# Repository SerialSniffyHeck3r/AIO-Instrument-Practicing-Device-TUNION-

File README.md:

# STM32F4 Portable Practice DSP Device

## Videos

https://www.youtube.com/watch?v=_CYvJwdOhUQ  Recovering Data

https://www.youtube.com/watch?v=7vPy3JID6l4  System Settings

https://www.youtube.com/watch?v=G-kPSslMNc0  BPM Auto Calculation

https://www.youtube.com/watch?v=HqbBY2KLgDY  Hardware Self Test

https://www.youtube.com/watch?v=8V4moodQUs4  Music Play Mode

https://www.youtube.com/watch?v=r6egSswZjCg  Notch Filter Applied

https://www.youtube.com/watch?v=-oUxMyITEes  Pitch Shifter Applied

https://www.youtube.com/watch?v=r_tZYo8vfbs  Volume Sound Effect

## Overview

This was developed for my bachelor graduation project, but with keeping in mind that the device will be used personally.. or crowdfunded.
It turned out it wasn't that good to be crowdfunded.. but still it works! and also good for my personal use.

This project focuses on developing a **portable practice companion** built around an **STM32F407** microcontroller.  
The device helps people practice instruments at home or in a rehearsal room without that huge amount of bulky gears.

## TL;DR (for recruiters)

- **Platform:** STM32F407, dual I2S audio, RGB 16x2 LCD, LED bar, rotary encoder, Li-ion battery
- **Focus:** Real-time audio DSP for instrument practice (notch filter, pitch shift, mixer), tuner, metronome
- **Reliability:** Flash config storage with CRC and wear-leveling, backup SRAM snapshot, factory self-test mode
- **Result:** Fully working handheld prototype with custom PCB, firmware, and UX

## STM32F4 기반 악기 연습 장치 'Tunion': 한국어 설명

해당 레포지토리는 본인의 졸업 작품으로써 설게한 제품에 대해 다루고 있습니다.

가정 및 연습실 환경에서는 악기를 크게 연주할 수 없어 뮤트를 착용하거나 전자 악기를 연주하게 된다는 문제 의식에서 출발하였으며, 악기 케이스에 항상 휴대하고 다닐 수 있으면서 악기를 연주할 때 바로 꺼내서 사용할 수 있는 만능 장비를 목표로 개발되었습니다. 
- 반주를 듣고, 반주가 없을 때 아무 음원이나 틀어서 Notch Filter를 적용하여 본인이 연주하는 악기 대역만 잘라서 그 부분과 본인의 악기 소리를 같이 들으면서 연습하거나
- 비트 및 서브비트 등 다양한 기능이 포함된 메트로놈 소리를 들으면서 반주도 같이 듣고 그 소리에 맞춰 악기를 연습하거나
- 악기를 조율하거나
- 또는 악기를 적절한 온습도의 환경에서 보관할 수 있게 하는 것

을 목표로 두고 있습니다.

본 기기의 기능은 다음과 같습니다:
- 악기로부터 들어오는 악기 소리 아날로그 입력 / 음향기기로부터 들어오는 반주 입력을 믹싱 및 개별 볼륨 조절
- 반주에서 본인이 연주하고자 하는 악기 대역을 자를 수 있는 Notch Filter를 적용해서 악기 소리와 믹싱
- HSE를 통해 달성한 고정밀 메트로놈, Sub-Beat, Tap Tempo, 리타르단도 기능을 포함하는 시중에도 찾아보기 힘든 다기능 메트로놈
- 악기 튜너 및 펑션 제너레이터
- 환경설정 및 Flash와 백업 SRAM에 환경설정 다중 백업
- Real-Time Clock, 연습 시간 기록 기능
- 실제 생산을 위한 하드웨어 셀프 테스트 (RAM, Flash 접근 시간 테스트, LCD 및 오디오 출력 테스트)
- 스스로의 펌웨어를 알아서 '죽이는' 히든 커맨드

### 기기 내부 저장 방식

본인을 레트로 컴퓨팅에 관심이 많으며, 레트로 컴퓨팅을 연구하거나 임베디드 시스템을 개인적으로 연구하면서 생긴 아이디어를 적용했습니다.

MCU와 내부 RAM이 살아 있는 상황에서
- Flash에 저장하는 경우: 홈 화면으로 복귀 / 절전 모드에서 탈출했을 때 설정 값이 이전과 변화했을 경우에만 Write
- BKPSRAM에 저장하는 경우: 모든 버튼이 조작되었을 때. Overhead가 낮아 최대 1초에 30번을 조작해도 시스템의 동작 안정성을 저해하지 않는다는 판단.

전원이 완전히 차단되었으나 백업 전지는 살아 있는 경우:
- 전원 인가시 BKPSRAM의 값 확인 후, Magic Number (0xDEADBEEF) Check
- 백업 전지가 살아 있으므로 Magic Number가 그대로 있으므로 유효하다고 판단하여, BKPSRAM에서 바로 값을 불러옴

전원이 완전히 차단되고 백업 배터리까지 빠졌을 경우:
- 전원 인가시 BKPSRAM의 값 확인 후 Magic Number가 유효하지 않음을 확인
- 사용자에게 Recover Data? YES / NO 인터페이스를 통해, 백업 배터리 분리가 초기화를 위한 의도적 행동인지 확인.
- 만약 YES를 선택했을 경우, FLASH에서 값을 복원. NO를 선택했을 경우 시스템 설정이 출고 시와 동일하게 초기화됨.
- 어차피 백업 배터리가 분리되었으면 **당연히** RTC도 유효하지 않을 것이므로, Yes / No 선택 유무에 상관없이 시계 재설정 유도
- 이후 정상 부팅 

---

## Backstory

I play lots of instrument from woodwinds to percussion. Music is pretty much literally my life. 
When I practice guitar or other instruments at home, 
I usually need shitloads of separate devices: audio interface, mixer, tuner, metronome, maybe a laptop? a phone??

So this is the backstory. I just wanted a **single small device** that can do all of these, while maintaining the functionality.
This is a graduation project, but my intention was to make something that is actually useful and is potentially lucrative.

The function that I planned to implement was:
- mix backing track and my instrument,
- remove some frequency range (for example vocals),
- quickly transpose the song,
- show audio level
- tuner and metromone with lots of features
- features that every portable embedded device that is on sale should have

So I designed and built this device as my **bachelor graduation project**.

---

## What this device does

From a user point of view, this box is:

- A **small mixer** for two stereo audio sources
- A **practice helper** that can cut or change a specific frequency band, then mix audio with my instrument sound
- A **digital tuner** with 1 cent resolution
- A **metronome** with different time signatures and tempo changes
- A **status monitor** for battery, temperature, humidity and system state

All of this runs on one STM32F407 MCU with no external DSP chip.

---

## Main features

### 1. Real-time audio DSP pipeline

- Two I2S inputs (for example: backing track + instrument/mic)
- DMA double-buffered ring pipeline (16-bit audio → float → processed → 16-bit)
- **Real-time mixing** of both channels with:
  - 50-step digital volume for each channel
  - master volume and balance
  - dBFS level meters for input level check

### 2. Adjustable band-cut / notch filter for practice

- User can select a **frequency range to cut** (for example vocal range)
- Implemented with **ARM CMSIS-DSP IIR biquad filters**
- Supports:
  - on/off control from the UI
  - start / end frequency
  - **three user presets** per instrument (saved in non-volatile memory)

This lets me listen to a song while removing or reducing the part I want to practice over.

### 3. Simple pitch shift for fast transposition

- Integrated **pitch shift** engine for quick transpose
- Control in **semitones** (for example −3…+3)
- Focus is on **low latency** and “good enough for practice”,  
  not studio-quality offline processing

### 4. Integrated tuner

- **Digital chromatic tuner** with 1-cent resolution
- AMDF-based pitch detection with:
  - harmonic / octave correction
  - pre-lock and lock logic to avoid jumping notes
- Adjustable:
  - **A4 base frequency** (calibration)
  - input sensitivity

The tuner drives both the LCD and the LED bar for visual feedback.

### 5. Sample-accurate metronome & tone generator

- Metronome audio is generated **inside the same DSP pipeline** as the audio
- Features:
  - accents and sub-clicks
  - tempo changes (ritardando / accelerando / back to a-tempo)
  - separate metronome volume
- Extra **sound generator mode** (sine / square / triangle)  
  for tuning or quick tests.

### 6. User interface and UX

- **RGB 16x2 character LCD** (HD44780-compatible)
  - custom UI pages for each mode (practice, tuner, metronome, settings)
- **LED bar** driven by PWM:
  - VU meter for input / mic levels
  - tuner center indication
  - metronome visualization
- **Rotary encoder + buttons**:
  - used for navigation and parameter editing
  - single short/long click design so it can be used while holding an instrument

I tried to keep the UI simple enough to use with one hand.

### 7. Power, environment and settings

- Powered from a **single Li-ion battery**
- Battery:
  - voltage measurement and level estimation
  - low-battery handling
- **Temperature & humidity** sensor (DHT22):
  - shows instrument storage environment
- **Config storage:**
  - main storage in Flash (sector with custom format)
  - record format with version, sequence number and CRC32
  - background service that only writes when values changed
- **Backup snapshot:**
  - second copy in backup SRAM,  
    so the device can restore settings quickly after a battery change

### 8. Factory / test mode

- Hidden button combo opens a **self-test mode**
- Used for:
  - LCD and LED test
  - audio path test
  - peripheral checks
- This was designed with **future production / repair** in mind.

---

## Hardware overview

- MCU: **STM32F407** (Cortex-M4 with FPU and DSP extensions)
- Audio:
  - Dual I2S interface
  - 16-bit stereo in/out
- UI:
  - HD44780-compatible RGB 16x2 LCD
  - 10-segment (or similar) LED bar
  - rotary encoder + buttons
- Sensors:
  - DHT22 temperature / humidity
  - battery voltage measurement
- Power:
  - Li-ion battery
  - backup power for RTC and SRAM

Custom PCB was designed so that the device is actually **hand-held and portable**. 

---

## Firmware / code structure (short version)

The firmware is written in **C** using the STM32 HAL and CMSIS-DSP.

- `main.c`  
  - main UI state machine, mode handling, LCD updates
- `notch.c`  
  - audio DSP pipeline, I2S callback, mixing, notch filter, pitch shift, metronome, sound generator
- `tuner.c`  
  - pitch detection and note / cent calculation
- `LEDcontrol.c`  
  - LED bar effects, VU meter and tuner / metronome visualization
- `BatteryTemp.c`, `dht.c`  
  - battery and DHT22 handling
- `PowerFlash.c`  
  - Flash config storage with CRC and wear-leveling
- `PowerSave.c`  
  - backup SRAM snapshot for fast resume
- `Clock.c`  
  - RTC time setting UI

The code is clearly not perfect, as this is one of my first huge system architect project.
but it is a complete prototype that I could really use as my **daily practice companion**.

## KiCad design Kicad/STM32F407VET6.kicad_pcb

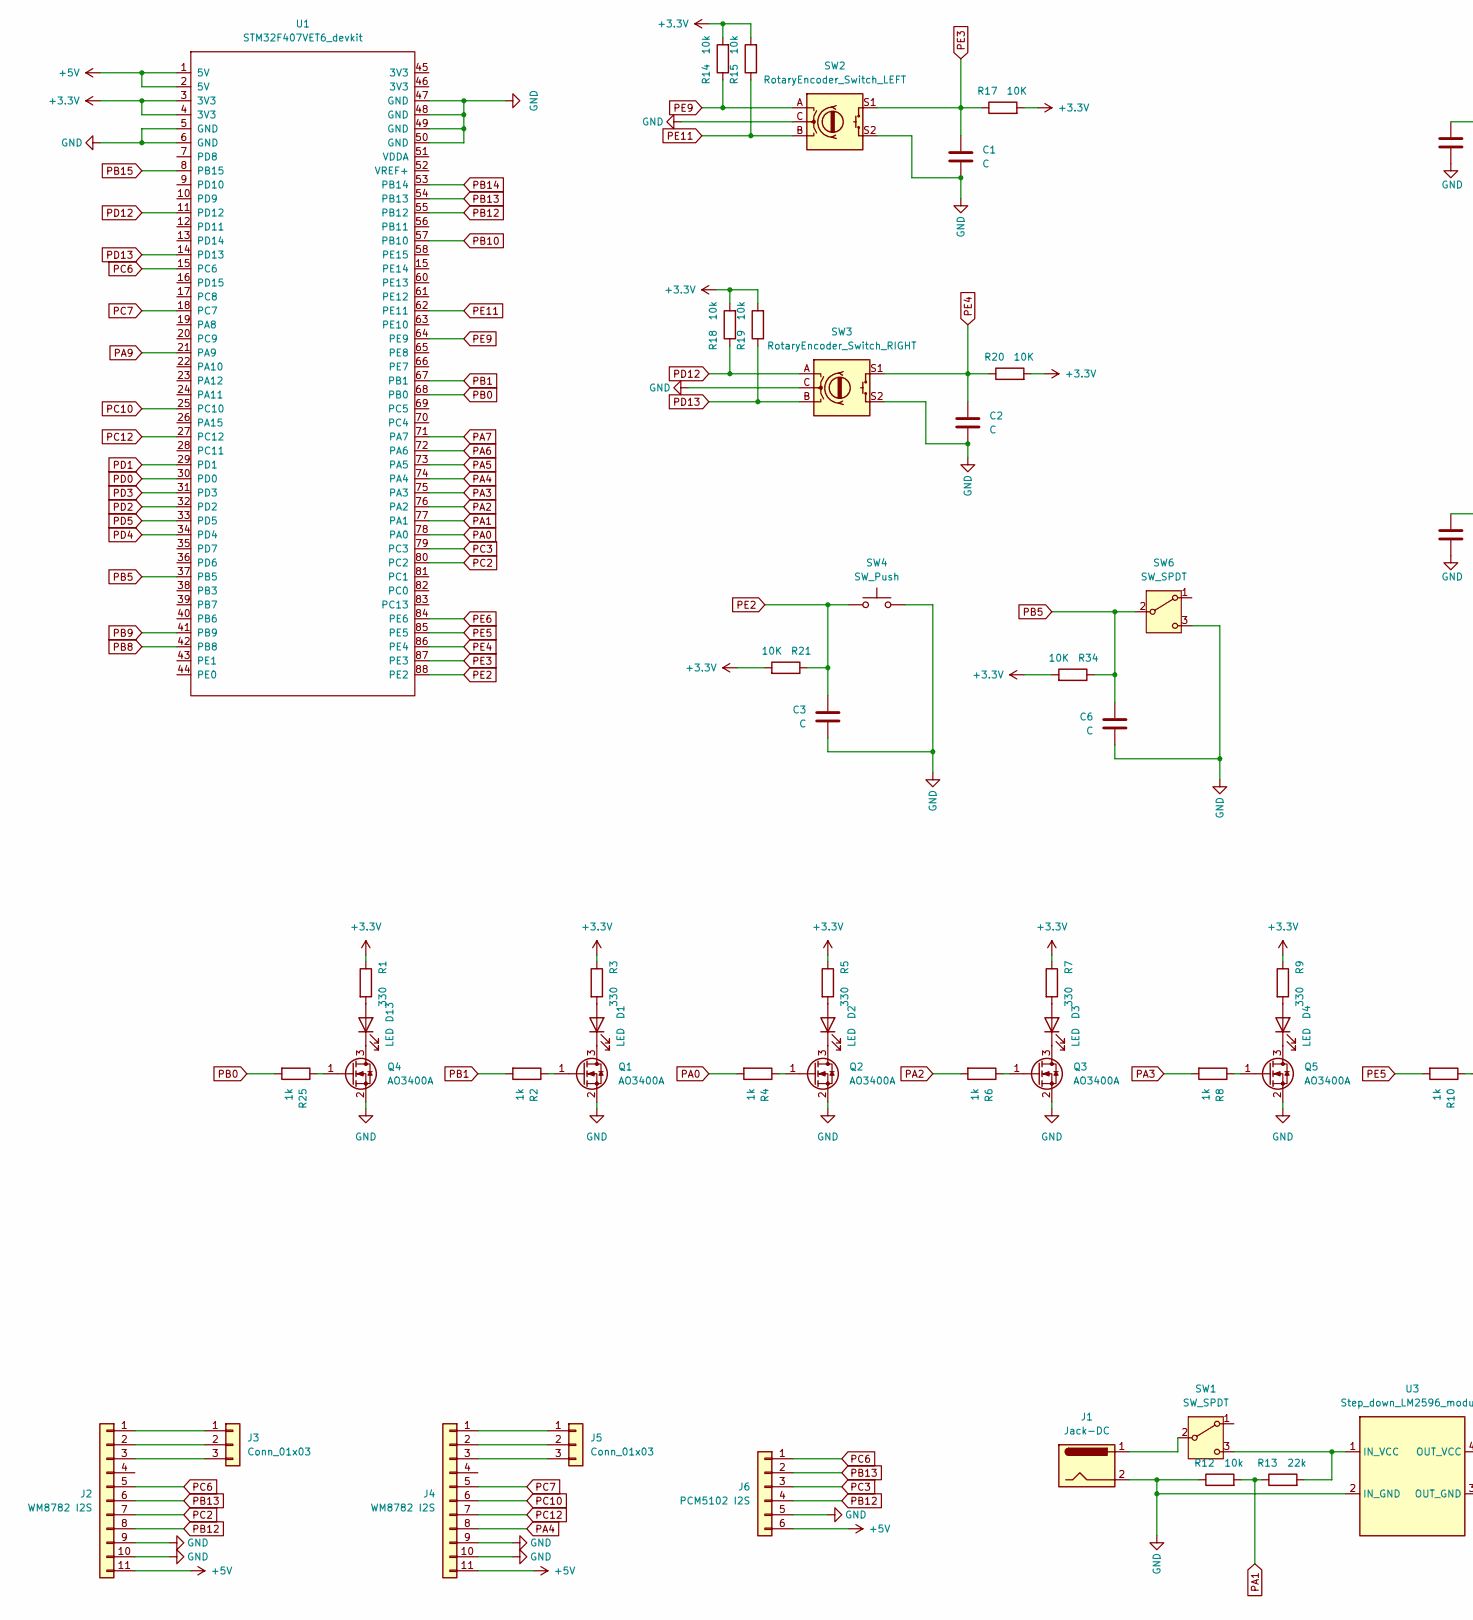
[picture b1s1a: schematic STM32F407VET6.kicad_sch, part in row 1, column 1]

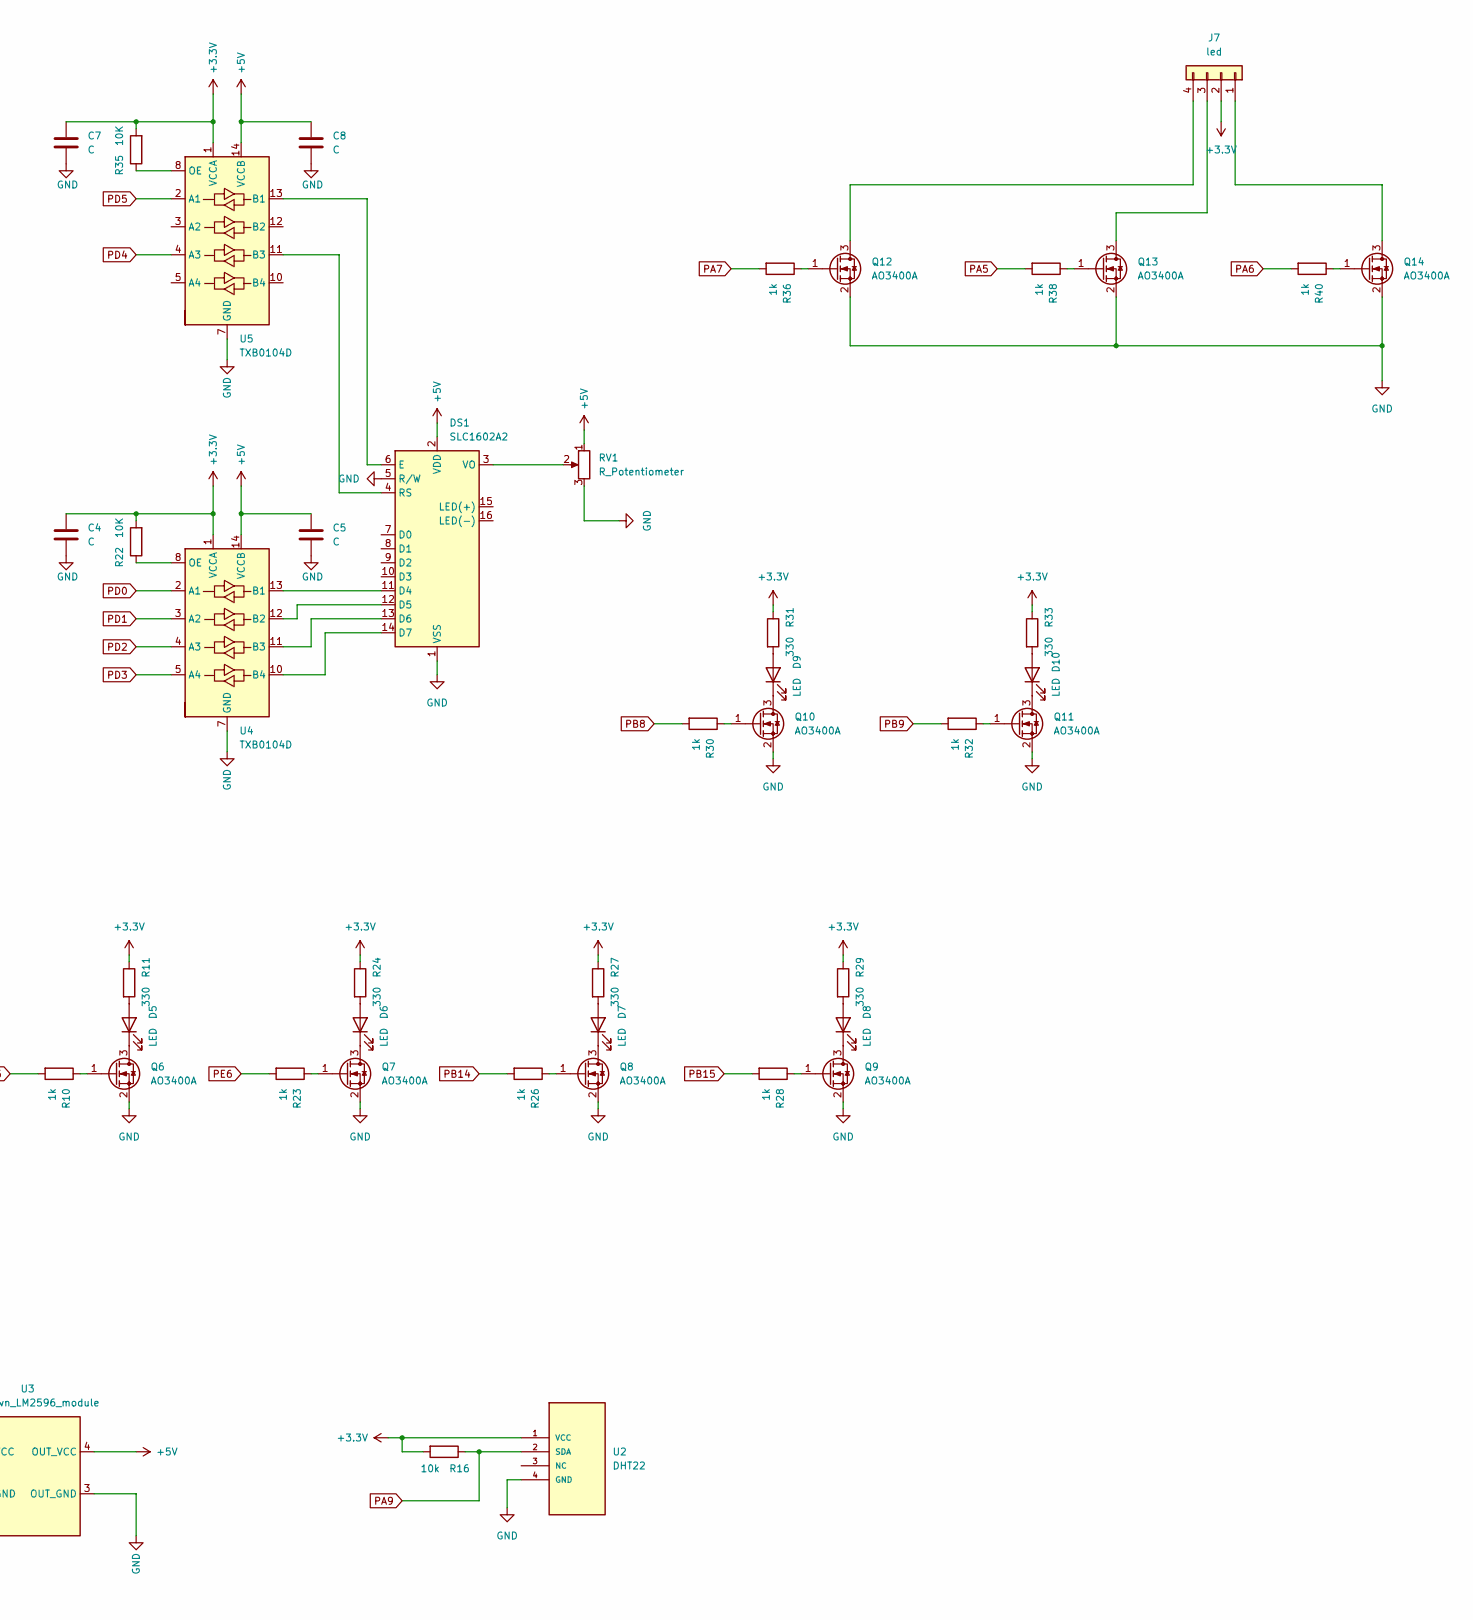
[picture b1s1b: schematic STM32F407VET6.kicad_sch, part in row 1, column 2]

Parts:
C1, C2, C3, C4, C5, C6, C7, C8: C; C_0603_1608Metric
D1, D2, D3, D4, D5, D6, D7, D8, D9, D10, D13: LED; LED_D5.0mm
DS1: SLC1602A2; WC1602A
J1: Jack-DC; BarrelJack_CUI_PJ-102AH_Horizontal
J2, J4: WM8782 I2S; wholesale I2S ADC
J3, J5: Conn_01x03; PinHeader_1x03_P2.54mm_Vertical
J6: PCM5102 I2S; PCM5102A DAC
J7: led; LED_D5.0mm-4_RGB_Wide_Pins
Q1, Q2, Q3, Q4, Q5, Q6, Q7, Q8, Q9, Q10, Q11, Q12, Q13, Q14: AO3400A; SOT-23
R1, R3, R5, R7, R9, R11, R24, R27, R29, R31, R33: 330; R_0603_1608Metric
R2, R4, R6, R8, R10, R23, R25, R26, R28, R30, R32, R36, R38, R40: 1k; R_0603_1608Metric
R12, R14, R15, R16, R18, R19: 10k; R_0603_1608Metric
R13: 22k; R_0603_1608Metric
R17, R20, R21, R22, R34, R35: 10K; R_0603_1608Metric
RV1: R_Potentiometer; Potentiometer_Vishay_T73YP_Vertical
SW1, SW6: SW_SPDT; SW_slide_3
SW2: RotaryEncoder_Switch_LEFT; RotaryEncoder_Alps_EC11E-Switch_Vertical_H20mm
SW3: RotaryEncoder_Switch_RIGHT; RotaryEncoder_Alps_EC11E-Switch_Vertical_H20mm
SW4: SW_Push; SW_PUSH-12mm_Wuerth-430476085716
U1: STM32F407VET6_devkit; STM32F407_DEV_KIT
U2: DHT22
U3: Step_down_LM2596_module; DCDC_LM2596
U4, U5: TXB0104D; SOIC-14_3.9x8.7mm_P1.27mm

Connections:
+3.3V: C4.1, C7.1, J7.2, R1.1, R3.1, R5.1, R7.1, R9.1, R11.1, R14.2, R15.2, R16.2, R17.2, R18.2, R19.2, R20.2, R21.2, R22.2, R24.1, R27.1, R29.1, R31.1, R33.1, R34.2, R35.2, U1.3 (3V3), U1.4 (3V3), U2.1 (VCC), U4.1 (VCCA), U5.1 (VCCA)
+5V: C5.1, C8.1, DS1.2 (VDD), J2.11, J4.11, J6.6, RV1.1, U1.1 (5V), U1.2 (5V), U3.4 (OUT_VCC), U4.14 (VCCB), U5.14 (VCCB)
GND: C1.2, C2.2, C3.2, C4.2, C5.2, C6.2, C7.2, C8.2, DS1.1 (VSS), DS1.5 (R/W), J1.2, J2.9, J2.10, J4.9, J4.10, J6.5, Q1.2 (S), Q2.2 (S), Q3.2 (S), Q4.2 (S), Q5.2 (S), Q6.2 (S), Q7.2 (S), Q8.2 (S), Q9.2 (S), Q10.2 (S), Q11.2 (S), Q12.2 (S), Q13.2 (S), Q14.2 (S), R12.1, RV1.3, SW2.C, SW2.S2, SW3.C, SW3.S2, SW4.2, SW6.3 (C), U1.5 (GND), U1.6 (GND), U1.47 (GND), U1.48 (GND), U1.49 (GND), U1.50 (GND), U2.4 (GND), U3.2 (IN_GND), U3.3 (OUT_GND), U4.7 (GND), U5.7 (GND)
unnamed: D1.2 (A), R3.2
unnamed: D1.1 (K), Q1.3 (D)
unnamed: D2.2 (A), R5.2
unnamed: D2.1 (K), Q2.3 (D)
unnamed: D3.2 (A), R7.2
unnamed: D3.1 (K), Q3.3 (D)
unnamed: D4.2 (A), R9.2
unnamed: D4.1 (K), Q5.3 (D)
unnamed: D5.2 (A), R11.2
unnamed: D5.1 (K), Q6.3 (D)
unnamed: D6.2 (A), R24.2
unnamed: D6.1 (K), Q7.3 (D)
unnamed: D7.2 (A), R27.2
unnamed: D7.1 (K), Q8.3 (D)
unnamed: D8.2 (A), R29.2
unnamed: D8.1 (K), Q9.3 (D)
unnamed: D9.2 (A), R31.2
unnamed: D9.1 (K), Q10.3 (D)
unnamed: D10.2 (A), R33.2
unnamed: D10.1 (K), Q11.3 (D)
unnamed: D13.2 (A), R1.2
unnamed: D13.1 (K), Q4.3 (D)
unnamed: DS1.11 (D4), U4.13 (B1)
unnamed: DS1.12 (D5), U4.12 (B2)
unnamed: DS1.13 (D6), U4.11 (B3)
unnamed: DS1.14 (D7), U4.10 (B4)
unnamed: DS1.6 (E), U5.13 (B1)
unnamed: DS1.4 (RS), U5.11 (B3)
unnamed: DS1.3 (VO), RV1.2
unnamed: J2.1, J3.1
unnamed: J2.2, J3.2
unnamed: J2.3, J3.3
unnamed: J4.1, J5.1
unnamed: J4.2, J5.2
unnamed: J4.3, J5.3
unnamed: J7.1, Q14.3 (D)
unnamed: J7.3, Q13.3 (D)
unnamed: J7.4, Q12.3 (D)
unnamed: Q1.1 (G), R2.1
unnamed: Q2.1 (G), R4.1
unnamed: Q3.1 (G), R6.1
unnamed: Q4.1 (G), R25.1
unnamed: Q5.1 (G), R8.1
unnamed: Q6.1 (G), R10.1
unnamed: Q7.1 (G), R23.1
unnamed: Q8.1 (G), R26.1
unnamed: Q9.1 (G), R28.1
unnamed: Q10.1 (G), R30.1
unnamed: Q11.1 (G), R32.1
unnamed: Q12.1 (G), R36.1
unnamed: Q13.1 (G), R38.1
unnamed: Q14.1 (G), R40.1
unnamed: J1.1, SW1.2 (B)
unnamed: R13.2, SW1.3 (C), U3.1 (IN_VCC)
unnamed: R22.1, U4.8 (OE)
unnamed: R35.1, U5.8 (OE)
PA0: R4.2, U1.78 (PA0)
PA1: R12.2, R13.1, U1.77 (PA1)
PA2: R6.2, U1.76 (PA2)
PA3: R8.2, U1.75 (PA3)
PA4: J4.8, U1.74 (PA4)
PA5: R38.2, U1.73 (PA5)
PA6: R40.2, U1.72 (PA6)
PA7: R36.2, U1.71 (PA7)
PA9: R16.1, U1.21 (PA9), U2.2 (SDA)
PB0: R25.2, U1.68 (PB0)
PB1: R2.2, U1.67 (PB1)
PB5: C6.1, R34.1, SW6.2 (B), U1.37 (PB5)
PB8: R30.2, U1.42 (PB8)
PB9: R32.2, U1.41 (PB9)
PB10: U1.57 (PB10)
PB12: J2.8, J6.4, U1.55 (PB12)
PB13: J2.6, J6.2, U1.54 (PB13)
PB14: R26.2, U1.53 (PB14)
PB15: R28.2, U1.8 (PB15)
PC2: J2.7, U1.80 (PC2)
PC3: J6.3, U1.79 (PC3)
PC6: J2.5, J6.1, U1.15 (PC6)
PC7: J4.5, U1.18 (PC7)
PC10: J4.6, U1.25 (PC10)
PC12: J4.7, U1.27 (PC12)
PD0: U1.30 (PD0), U4.2 (A1)
PD1: U1.29 (PD1), U4.3 (A2)
PD2: U1.32 (PD2), U4.4 (A3)
PD3: U1.31 (PD3), U4.5 (A4)
PD4: U1.34 (PD4), U5.4 (A3)
PD5: U1.33 (PD5), U5.2 (A1)
PD12: R18.1, SW3.A, U1.11 (PD12)
PD13: R19.1, SW3.B, U1.14 (PD13)
PE2: C3.1, R21.1, SW4.1, U1.88 (PE2)
PE3: C1.1, R17.1, SW2.S1, U1.87 (PE3)
PE4: C2.1, R20.1, SW3.S1, U1.86 (PE4)
PE5: R10.2, U1.85 (PE5)
PE6: R23.2, U1.84 (PE6)
PE9: R14.1, SW2.A, U1.64 (PE9)
PE11: R15.1, SW2.B, U1.62 (PE11)

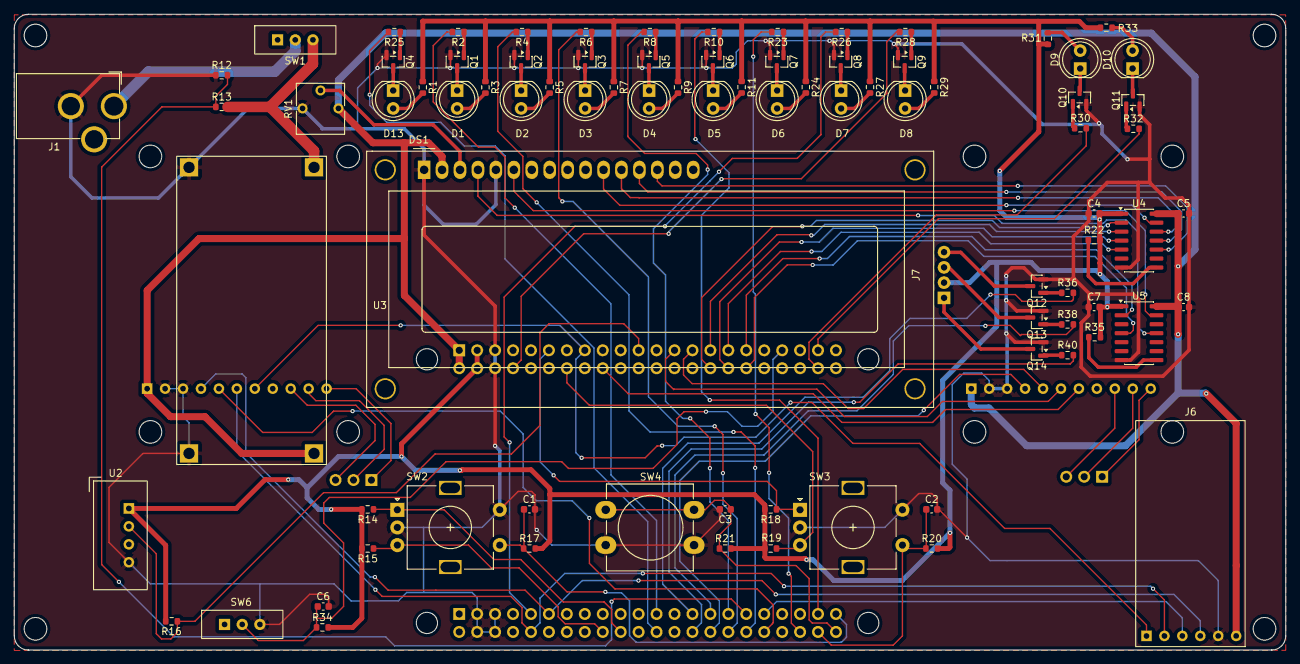
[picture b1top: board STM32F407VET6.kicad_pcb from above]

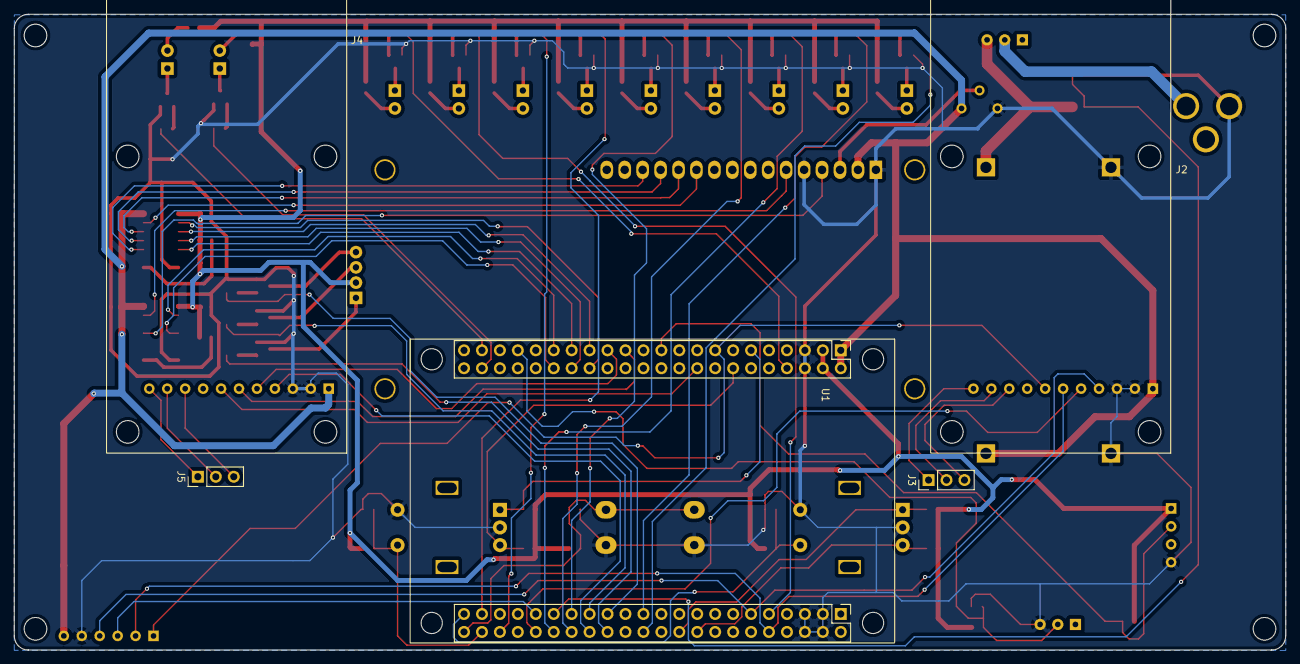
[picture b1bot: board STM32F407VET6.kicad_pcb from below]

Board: 2 copper layers, 180.0 x 90.0 mm, 90 parts (5 on the bottom side), 98 nets.

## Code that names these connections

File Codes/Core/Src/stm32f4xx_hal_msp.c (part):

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
    __HAL_RCC_GPIOA_CLK_ENABLE();
    /**ADC1 GPIO Configuration
    PA1     ------> ADC1_IN1
    */
    GPIO_InitStruct.Pin = GPIO_PIN_1;
    GPIO_InitStruct.Mode = GPIO_MODE_ANALOG;
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    __HAL_RCC_ADC1_CLK_DISABLE();

    /**ADC1 GPIO Configuration
    PA1     ------> ADC1_IN1
    */
    HAL_GPIO_DeInit(GPIOA, GPIO_PIN_1);

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    __HAL_RCC_GPIOC_CLK_ENABLE();
    __HAL_RCC_GPIOB_CLK_ENABLE();
    /**I2S2 GPIO Configuration
    PC2     ------> I2S2_ext_SD
    PC3     ------> I2S2_SD
    PB12     ------> I2S2_WS
    PB13     ------> I2S2_CK
    PC6     ------> I2S2_MCK
    */
    GPIO_InitStruct.Pin = GPIO_PIN_2;
    GPIO_InitStruct.Mode = GPIO_MODE_AF_PP;
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    __HAL_RCC_GPIOA_CLK_ENABLE();
    __HAL_RCC_GPIOC_CLK_ENABLE();
    /**I2S3 GPIO Configuration
    PA4     ------> I2S3_WS
    PC7     ------> I2S3_MCK
    PC10     ------> I2S3_CK
    PC12     ------> I2S3_SD
    */
    GPIO_InitStruct.Pin = GPIO_PIN_4;
    GPIO_InitStruct.Mode = GPIO_MODE_AF_PP;
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    __HAL_RCC_SPI2_CLK_DISABLE();

    /**I2S2 GPIO Configuration
    PC2     ------> I2S2_ext_SD
    PC3     ------> I2S2_SD
    PB12     ------> I2S2_WS
    PB13     ------> I2S2_CK
    PC6     ------> I2S2_MCK
    */
    HAL_GPIO_DeInit(GPIOC, GPIO_PIN_2|GPIO_PIN_3|GPIO_PIN_6);

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    __HAL_RCC_SPI3_CLK_DISABLE();

    /**I2S3 GPIO Configuration
    PA4     ------> I2S3_WS
    PC7     ------> I2S3_MCK
    PC10     ------> I2S3_CK
    PC12     ------> I2S3_SD
    */
    HAL_GPIO_DeInit(GPIOA, GPIO_PIN_4);

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
    __HAL_RCC_GPIOE_CLK_ENABLE();
    /**TIM1 GPIO Configuration
    PE9     ------> TIM1_CH1
    PE11     ------> TIM1_CH2
    */
    GPIO_InitStruct.Pin = GPIO_PIN_9|GPIO_PIN_11;
    GPIO_InitStruct.Mode = GPIO_MODE_AF_PP;
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
    __HAL_RCC_GPIOD_CLK_ENABLE();
    /**TIM4 GPIO Configuration
    PD12     ------> TIM4_CH1
    PD13     ------> TIM4_CH2
    */
    GPIO_InitStruct.Pin = GPIO_PIN_12|GPIO_PIN_13;
    GPIO_InitStruct.Mode = GPIO_MODE_AF_PP;
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    /* USER CODE END TIM3_MspPostInit 0 */
    __HAL_RCC_GPIOB_CLK_ENABLE();
    /**TIM3 GPIO Configuration
    PB0     ------> TIM3_CH3
    PB1     ------> TIM3_CH4
    */
    GPIO_InitStruct.Pin = GPIO_PIN_0|GPIO_PIN_1;
    GPIO_InitStruct.Mode = GPIO_MODE_AF_PP;
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
    __HAL_RCC_GPIOA_CLK_ENABLE();
    /**TIM5 GPIO Configuration
    PA0-WKUP     ------> TIM5_CH1
    PA2     ------> TIM5_CH3
    PA3     ------> TIM5_CH4
    */
    GPIO_InitStruct.Pin = GPIO_PIN_0|GPIO_PIN_2|GPIO_PIN_3;
    GPIO_InitStruct.Mode = GPIO_MODE_AF_PP;
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
    __HAL_RCC_GPIOE_CLK_ENABLE();
    /**TIM9 GPIO Configuration
    PE5     ------> TIM9_CH1
    PE6     ------> TIM9_CH2
    */
    GPIO_InitStruct.Pin = GPIO_PIN_5|GPIO_PIN_6;
    GPIO_InitStruct.Mode = GPIO_MODE_AF_PP;
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
    __HAL_RCC_GPIOB_CLK_ENABLE();
    /**TIM12 GPIO Configuration
    PB14     ------> TIM12_CH1
    PB15     ------> TIM12_CH2
    */
    GPIO_InitStruct.Pin = GPIO_PIN_14|GPIO_PIN_15;
    GPIO_InitStruct.Mode = GPIO_MODE_AF_PP;
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    __HAL_RCC_TIM1_CLK_DISABLE();

    /**TIM1 GPIO Configuration
    PE9     ------> TIM1_CH1
    PE11     ------> TIM1_CH2
    */
    HAL_GPIO_DeInit(GPIOE, GPIO_PIN_9|GPIO_PIN_11);

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    __HAL_RCC_TIM4_CLK_DISABLE();

    /**TIM4 GPIO Configuration
    PD12     ------> TIM4_CH1
    PD13     ------> TIM4_CH2
    */
    HAL_GPIO_DeInit(GPIOD, GPIO_PIN_12|GPIO_PIN_13);

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
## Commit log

2026-03-01 Update README with project overview and features
    Add detailed project description and features for STM32F4 DSP device
2026-03-01 Create Codes
2026-03-01 Create Kicad
2026-03-01 Create Media
2026-03-01 Update README for clarity on device and code
    Clarified descriptions of the device's portability and code quality.
2026-03-01 Revise README for clarity and detail
    Updated project description for clarity and improved readability.
2026-03-01 Rename Screenshot 2026-03-02 061731.png to Screenshot.png

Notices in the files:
Codes/Core/Src/stm32f4xx_hal_msp.c:
Copyright (c) 2025 STMicroelectronics.
All rights reserved.
This software is licensed under terms that can be found in the LICENSE file
